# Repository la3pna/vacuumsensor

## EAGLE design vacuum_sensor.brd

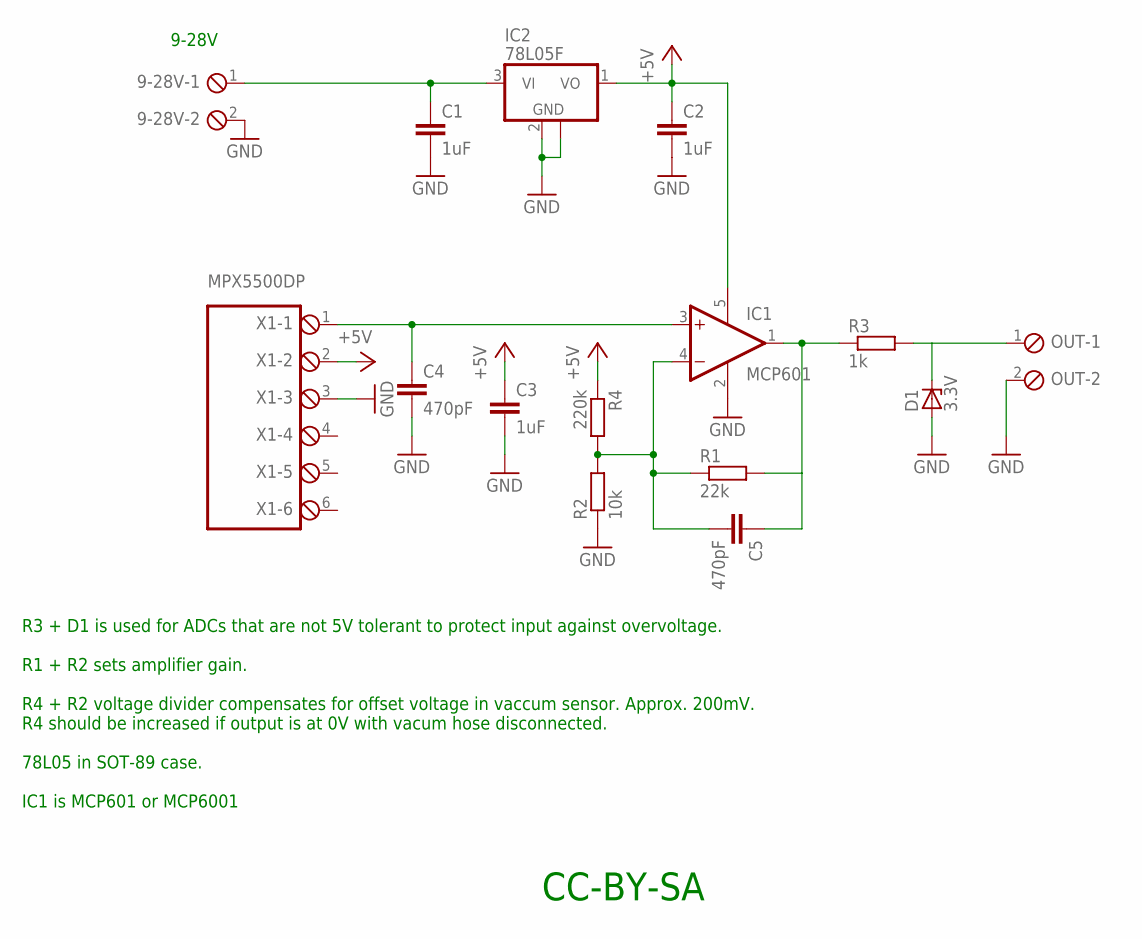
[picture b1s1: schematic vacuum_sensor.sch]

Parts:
9-28V: MPT2; 2POL254
C1, C2, C3: 1uF; C0805
C4, C5: 470pF; C0805
D1: 3.3V; SOT23
IC1: MCP601; SOT23-5
IC2: 78L05F; SOT89
OUT: MPT2; 2POL254
R1: 22k; R0805
R2: 10k; R0805
R3: 1k; R0805
R4: 220k; R0805
X1: MPT6; 6POL254

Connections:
+5V: C2.1, C3.1, IC1.5 (V+), IC2.1 (VO), R4.1, X1.2
GND: 9-28V.2, C1.2, C2.2, C3.2, C4.2, D1.1 (A), IC1.2 (V-), IC2.2 (GND), IC2.2@1 (GND), OUT.2, R2.1, X1.3
unnamed: C5.2, IC1.4 (-IN), R1.1, R2.2, R4.2
unnamed: 9-28V.1, C1.1, IC2.3 (VI)
unnamed: C5.1, IC1.1 (OUT), R1.2, R3.1
unnamed: C4.1, IC1.3 (+IN), X1.1
unnamed: D1.3 (C), OUT.1, R3.2

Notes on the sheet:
MPX5500DP
9-28V
R3 + D1 is used for ADCs that are not 5V tolerant to protect input against overvoltage. R1 + R2 sets amplifier gain. R4 + R2 voltage divider compensates for offset voltage in vaccum sensor. Approx. 200mV. R4 should be increased if output is at 0V with vacum hose disconnected. 78L05 in SOT-89 case. 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
CC-BY-SA

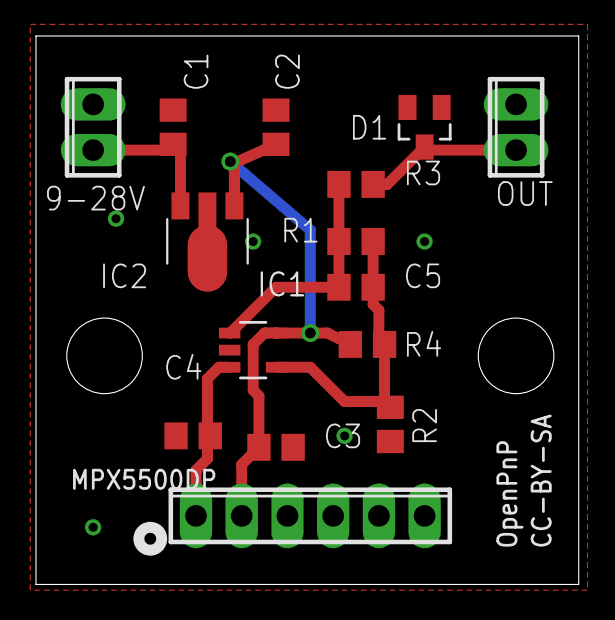
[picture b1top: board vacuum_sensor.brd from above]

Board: 2 copper layers, 30.1 x 30.5 mm, 15 parts (0 on the bottom side), 7 nets.

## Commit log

2017-01-29 schematic + board layout picture
2017-01-29 Eagle files
2017-01-29 arduino code
2017-01-29 PCB update
